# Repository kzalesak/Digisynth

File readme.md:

# Digisynth - the pocket Lunetta

A simple Lunetta-type synthesiser based on the 40106 integrated circuit, designed to fit into a pocket, with many configurable options.
Can be controlled by dials, light level and any resistive material. Contains a passive mixer and can utilise oscillator sync. 

You are invited to reproduce the PCB's and experiment yourself.

## Introduction
Lunettas emerged in the 60's/70's as a niche type of synth. They are named after the percussionist [Stanley Lunetta](http://moosack.net/), an experimenter at the boundaries of electronic music, and the father of the original Lunetta. There is a whole [amateur e-book](https://docs.google.com/document/d/1V9qerry_PsXTZqt_UDx7C-wcuMe_6_gyy6M_MyAgQoA/edit) dedicated to Lunettas, with various images and links.

Our pocket synth is based on the 40106 digital logic CMOS inverter, and has been inspired by Elliot Williams' great [digital synthesizer series on Hackaday](https://hackaday.com/2015/02/04/logic-noise-sweet-sweet-oscillator-sounds/). It has a nice detailed explanation of how the synth operates, as well as many expansion circuits, including multi octave synths, sequencers, drums, filters and VCO's. I have some of the components available in surplus and may be able to provide some of them for your builds, or at least point you to good sources of components if you contact me.

## Design information
### Prerequisites
#### View and edit
In order to view and edit the files you are going to need the free open source circuitry tool KiCAD, available from http://kicad.org/
It is best viewed with version 5.0 and above.

#### Make copies
If all you're after are the build files (Gerber and drill files) which can be sent to a PCB (Printed Circuit Board) manufacturer, they are located within the Gerbers sub-folder. All they need is to be zipped up and uploaded according to the manufacturer's instructions.

### Installing
Download the `Digisynth_PCB` folder and open the `Digisynth.pro` file. It should load cached libraries automatically. If this does not happen, add the `Digisynth-cache.lib` to your library path within KiCAD.
The Gerbers are located within `Digisynth_PCB/Gerbers`.

## Synth manual
The core of the synth consists of a digital logic inverter (NOT Gate) in a feedback loop. The inverter outputs a HIGH voltage on its output pin when there is LOW voltage on its input pin and vice versa. Connecting the input and output pins together will create an oscillating circuit, switching between HIGH and LOW.<br>
A capacitor connected between the input pin and ground will take some time to charge/discharge after every voltage change, effectively slowing down the switching process. Placing a resistor between the input and output pin limits the current flowing to the capacitor allowing us to further control the charging/discharging time. Longer charging times mean lower frequency, so higher capacitor value (capacity) and higher resistor value (resistance) will both lead to lower frequencies.

The synth consists of various functional blocks, which can be roughly divided into oscillator units, audio blocks and special effect blocks.

### Oscillator units
In order to make the oscillator functional (in the audio range of frequencies), we must choose a capacitor and a resistor. To do this, we can connect jumpers (or some jumper wires), vertically across the pins at the bottom of the board. In the example setup below, the sections are highlighted in blue and connections are represented in red. The setup is using the __Low__ capacitor + __Potentiometer__ for __UNIT A__ and __Mid__ capacitor +  __Photoresistor__ for __UNIT B__.

The options you can select from are:
1. __Capacitors__
- __Low__ - on UNIT A
- __Mid__ - on UNIT A/B
- __High__ - on UNIT B
- __Custom capacitor__ - on UNIT A/B - This is a place where you can add an arbitrary capacitor. The lower pin is connected to `+` and the two upper pins are both connected to `-` (denoted as a white border on the board, here minus = ground), so be sure to place electrolytic capacitors with the right polarity.

When a capacitor is inserted into the *custom capacitor* slot, it always controls the frequency. If you select multiple capacitors, they will be connected in parallel, so their capacity will sum up.

2. __Resistors__
- <b>Potentiometer</b> - allows to control frequency via the appropriate knob (A or B). The resistance should be 0-100kOhm. 
- __Photoresistor__ - frequency control using light. The more light, the higher the tone.
- __Pads__ - the pads are a place to connect your own resistance. Try connecting them together with your fingers (9v is generally safe, unless wires pierce the skin), connecting them through a pencil track (alligator clips are good for this), or connecting them to wires and then running the wires to a stream of water from the tap. You could also build a little keyboard out of different resistors and switches. Feel free to experiment!

When you select multiple resistances, they get connected in parallel and their total resistance will _decrease_, so the frequency will increase. Varying the resistances is then [non-linear according to](https://www.desmos.com/calculator/lihhc9hmr2)  and can be used for interesting effects.

### Audio block
The audio control section consists of three sub blocks.

1. __Mixer__ - a simple passive audio mixer, which allows you to select whether to output sound from UNIT A, UNIT B, or both at the same time. When the two units are close in frequency (or close in an integer multiple of the frequency), you will get a phenomenon know as beats, where a third frequency can he heard arising. A typical view on an oscilloscope of two channels not close is frequency is:

2. __Divider__ - a simple voltage divider, which reduces the voltage from 9 V to about 1V, which is the standard pre-amplified audio level. To bypass this, run jumper wires (DuPont wires) directly from the mixer pins to the *Channel select* pins. This can be also used to connect UNIT A and B to different audio channels, allowing you to control the sound of the left and right speaker independently.
3. __Channel select__ - connects the divided output either to left, right, or both channels on your speakers.

The example above is connected to use UNIT A, UNIT B and both the left and right channel of the speakers.

### Special effects
1. __Decay effect__ - When the decay capacitor is added, an interesting envelope effect upon power off is created, a combination of decreasing volume and increasing frequency. Values of 1uF provide a short sliding end to a tone, values of 100uF produce a nice bouncy effect and 1000uF produce a 30 second slowly increasing slide. If the synthesiser was built with LED's, use larger capacitor values, as the LED's will drain the capacitor fast. Pay attention to the polarity, the negative lead position is marked white.
2. __Oscillator sync__ - when the sync pins are connected, the synth enters a special regime in which UNIT A controls the oscillation of UNIT B. In practice, on an oscilloscope, which plots voltage over time, we can see it as:

In the sync regime, UNIT B controls the pitch (base frequency) of the tone, while UNIT A controls the timbre (color of the tone). Varying the frequency of both can lead to many different effects, sometimes sounding nasal, sometimes resembling beeps, even beating like patterns. Note that UNIT B has to be at a frequency sufficiently higher then UNIT A. If you are not getting any sounds, try adjusting your capacitor/resistor values. You can either use the square or triangle wave (lower or upper pin) for your sync.

3. __Triangle wave__ - the pin labeled _SYNC ^_ (circled red in the image) is connected to the input pin of our IC (directly to the capacitor), unlike the output pin as usual. This gives us a good place to probe the triangle signal. Connecting this pin to the divider pin inside of the Audio Mixer section using a jumper wire (DuPont wire) allows us to send this signal to our speakers. It gives a much cleaner, but also quieter sound, closer to the natural sine waves musical instruments make.
Similarily, the SYNC \_|- pin is a good place to probe the square wave output of UNIT A. Viewed on an oscilloscope, the square wave in white, triangle in red:

### Extra functionality
1. The synth __does not have an ultrasound filter__, allowing you to use it as a source of a fast digital clock (a sequence of HIGH and LOW voltage), which can come in handy in many scenarios, e.g. when testing speeds of oscilloscopes. However, the sound this produces can annoy animals, like dogs, cats, and can be detrimental to the night navigation of bats, so make sure you turn off or disconnect your synth when you've finished buzzing.
2. On the other side of the board, there are pads to solder [surface mount device](https://en.wikipedia.org/wiki/Surface-mount_technology), SMD LED's. As this will interfere to some extent with the decay effect (you'll have to use larger capacitors), it is at your discretion to include it. To limit this, I recommend using a red or yellow LED, and a high value capacitor (~1k).
3. In the top left, pins labeled __V+__ and __GND__ are connected to the battery (V+ only when the synthesizer is on). It is a convenient place to store unjused jumpers, but also a convenient quick power source for any extensions to your synths / other projects.

## License

This project is licensed under the TAPR Open Hardware License (www.tapr.org/OHL).

## Acknowledgments

I would like to thank the [Institute of Making](https://www.instituteofmaking.org.uk/) for making it possible to design this synthesizer and build this synthesizer. I'd also like to thank Elliott Williams for his (already mentioned) [series on Hackaday](https://hackaday.com/2015/02/04/logic-noise-sweet-sweet-oscillator-sounds/), which provided the initial inspiration for this project.

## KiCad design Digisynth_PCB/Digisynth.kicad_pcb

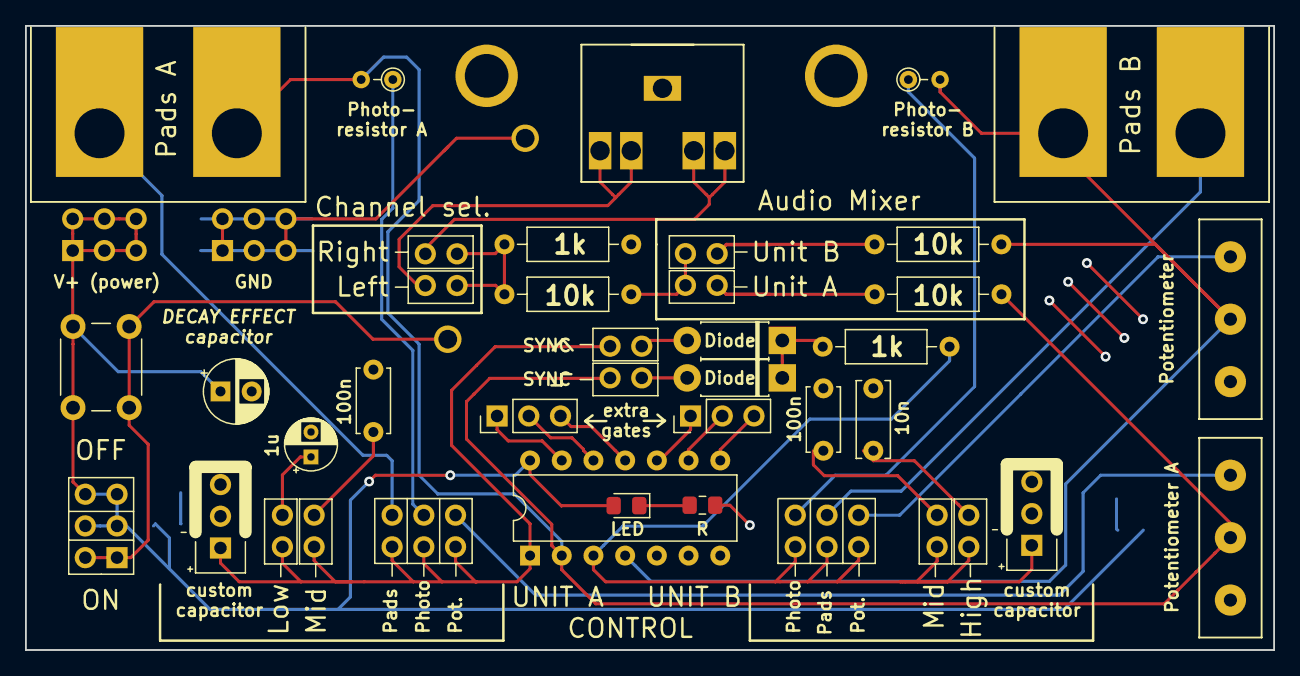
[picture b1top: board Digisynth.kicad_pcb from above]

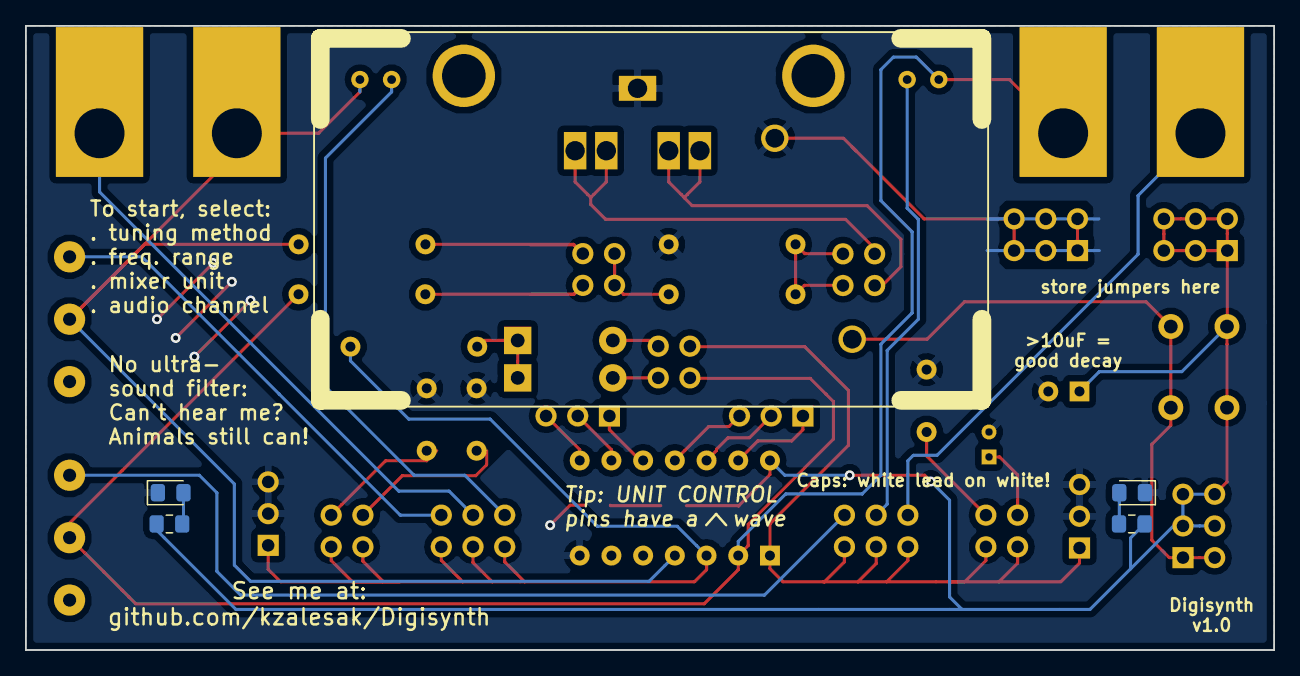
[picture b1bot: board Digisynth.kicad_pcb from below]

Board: 2 copper layers, 100.0 x 50.0 mm, 44 parts (5 on the bottom side), 35 nets.

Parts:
BT1: Battery; BatteryHolder_COMF_BH9VA_1x6F22(9V)_minimum
C1: 1u; CP_Radial_D4.0mm_P2.00mm
C2, C3: 100n; C_Disc_D5.0mm_W2.5mm_P5.00mm
C4: 10n; C_Disc_D6.0mm_W2.5mm_P5.00mm
C5: C_Var (Fem pin header); CP_Radial_D5.0mm_P2.50mm
D1, D5: D; D_DO-41_SOD81_P7.62mm_Horizontal
D2, D3, D4: LED; LED_0805_2012Metric_Pad1.15x1.40mm_HandSolder
J1, J4, J5, J8, J11: Conn_02x02_Counter_Clockwise; PinHeader_2x02_P2.54mm_Selector_CCW
J2, J7: Conn_01x03_Female; CAP_Changer
J3, J6: Conn_02x03_Counter_Clockwise; PinHeader_2x03_P2.54mm_Selector_CCW
J9, J10: Conn_02x04_Counter_Clockwise; Conn_02x03_CCW_NoSilk
J12: AudioJack3_Ground; JC-128
J13, J14: Conn_01x01_Female; BAT_PAD
J15, J16: Conn_01x03; PinHeader_1x03_P2.54mm_Vertical
R1, R3: R_PHOTO; R_Axial_DIN0204_L3.6mm_D1.6mm_P2.54mm_Vertical
R2, R8: 1k; R_Axial_DIN0207_L6.3mm_D2.5mm_P10.16mm_Horizontal
R4, R9, R10: R; R_0805_2012Metric_Pad1.15x1.40mm_HandSolder
R5, R6, R7: 10k; R_Axial_DIN0207_L6.3mm_D2.5mm_P10.16mm_Horizontal
RV1, RV2: R_POT; SR_PASSIVES_POT_PW1.00_P5.00
SW1: SW_Push; SW_PUSH_6mm
SW2: SW_SPDT; DPDT_Switch_2x03_P2.54mm
TP1, TP2: TestPoint_2Pole; ALICLIP_POINT
U1: 40106; DIP-14_W7.62mm

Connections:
/40106/8Dout: J16.3, U1.8
/40106/9Din: J16.2, U1.9
/40106/10Eout: J16.1, U1.10
/40106/11Ein: J15.3, U1.11
/40106/12Fout: J15.2, U1.12
/40106/13Fin: J15.1, U1.13
GND: C1.2, C2.2, C3.2, C4.2, C5.2, D3.1, D4.1, J2.2, J2.3, J7.2, J7.3, J9.1, J9.2, J9.3, J9.4, J9.5, J9.6, J12.S, J14.1, R4.2, R8.1, U1.7
IN_A: J1.1, J1.2, J2.1, J3.1, J3.2, J3.3, J4.2, U1.1
IN_B: J5.1, J5.2, J6.1, J6.2, J6.3, J7.1, R2.1, U1.3
unnamed: C1.1, J1.4
unnamed: C2.1, J1.3
unnamed: C3.1, J5.4
unnamed: C4.1, J5.3
unnamed: D1.1, D5.1, R2.2
unnamed: D1.2, J4.4
unnamed: D2.1, R4.1
unnamed: D3.2, R9.2
unnamed: D4.2, R10.2
unnamed: D5.2, J4.3
unnamed: J3.4, TP1.2
unnamed: J3.5, R1.1
unnamed: J3.6, RV1.3
unnamed: J6.4, R3.1
unnamed: J6.5, TP2.1
unnamed: J6.6, RV2.3
unnamed: J8.1, R5.1
unnamed: J8.2, R6.1
unnamed: J8.3, J8.4, R7.2
unnamed: J11.1, J12.T
unnamed: J11.2, J12.R
unnamed: J11.3, J11.4, R7.1, R8.2
unnamed: J13.1, SW1.2, SW2.1
OUT_A: J4.1, R1.2, R6.2, RV1.2, TP1.1, U1.2
OUT_B: R3.2, R5.2, RV2.2, TP2.2, U1.4
V+: C5.1, D2.2, J10.1, J10.2, J10.3, J10.4, J10.5, J10.6, R9.1, R10.1, SW1.1, SW2.2, SW2.3, U1.14

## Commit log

2019-02-22 KiCAD project and readme
2019-02-22 Add gerbers
2021-11-08 Update readme.md
    https://forum.kicad.info/t/warning-avoid-all-links-to-kicad-pcb-org-use-kicad-org/31521
